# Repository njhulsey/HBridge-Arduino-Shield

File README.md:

# HBridge-Arduino-Shield
During my senior year of highschool I entered the Science Olympiad Electric Vehicle competition. I wanted to make everything for this competition from scratch. My plan was to use as little "pre-made" parts as possible. To control the motors on my car, I made my own arduino H bridge shield. This allowed me to control the direction of each DC motor independently. The H-Bridge IC is the L239D. However, I did not end up using this board in the final competition, but I still learned a lot from making it. I designed the board in eagle and printed it in my highschools makerspace. 

You can read about the competition here: https://scioly.org/wiki/index.php/Electric_Vehicle 

WHAT I LEARNED:
- EAGLE circuit design
- How to use the L239D H Bridge IC
- Soldering
- Circuit board printing
- Learned more about the intricacies of DC motors

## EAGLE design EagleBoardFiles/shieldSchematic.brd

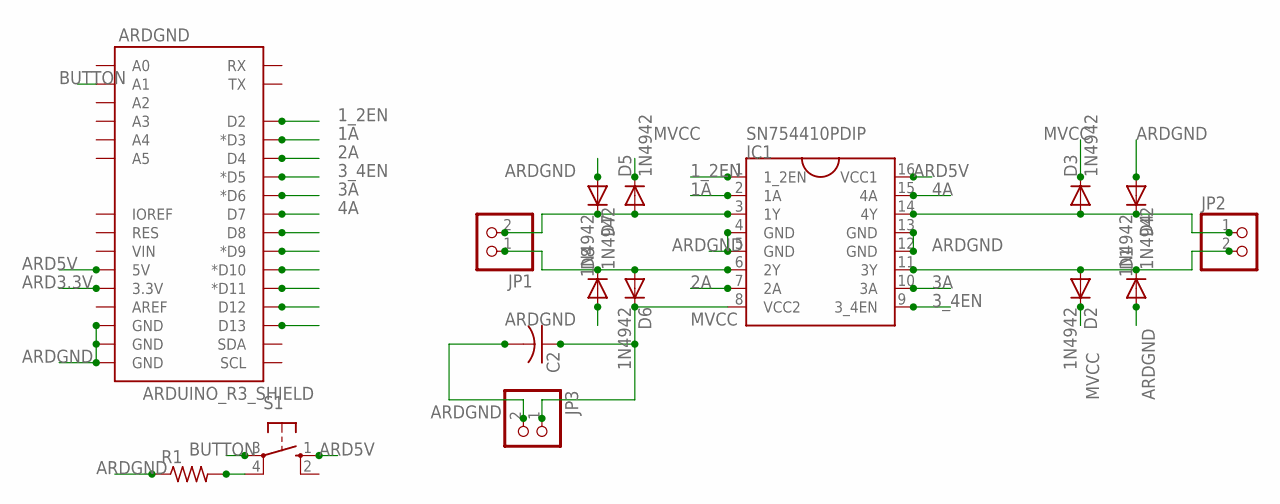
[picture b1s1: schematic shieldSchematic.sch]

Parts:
ARDGND: ARDUINO_R3_SHIELD; UNO_R3_SHIELD
C2: C-US025-024X044; C025-024X044
D1, D2, D3, D4, D5, D6, D7, D8: 1N4942; DO41-10
IC1: SN754410PDIP; DIL16
JP1, JP2, JP3: PINHD-1X2; 1X02
R1: R-US_0207/10; 0207/10
S1: 40-XX; B3F-40XX

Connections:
1A: ARDGND.D3 (*D3), IC1.2 (1A)
1_2EN: ARDGND.D2, IC1.1 (1_2EN)
2A: ARDGND.D4, IC1.7 (2A)
3A: ARDGND.D6 (*D6), IC1.10 (3A)
3_4EN: ARDGND.D5 (*D5), IC1.9 (3_4EN)
4A: ARDGND.D7, IC1.15 (4A)
ARD3.3V: ARDGND.3.3V
ARD5V: ARDGND.5V, IC1.16 (VCC1), S1.1 (S)
ARDGND: ARDGND.GND@0 (GND), ARDGND.GND@1 (GND), ARDGND.GND@2 (GND), C2.2, D1.A, D4.A, D7.A, D8.A, IC1.4 (GND), IC1.5 (GND), IC1.12 (GND), IC1.13 (GND), JP3.2, R1.1
BUTTON: ARDGND.A1, S1.3
MVCC: C2.1, D2.C, D3.C, D5.C, D6.C, IC1.8 (VCC2), JP3.1
unnamed: D5.A, D7.C, IC1.3 (1Y), JP1.2
unnamed: R1.2, S1.4 (P1)
unnamed: D6.A, D8.C, IC1.6 (2Y), JP1.1
unnamed: D1.C, D2.A, IC1.11 (3Y), JP2.2
unnamed: D3.A, D4.C, IC1.14 (4Y), JP2.1

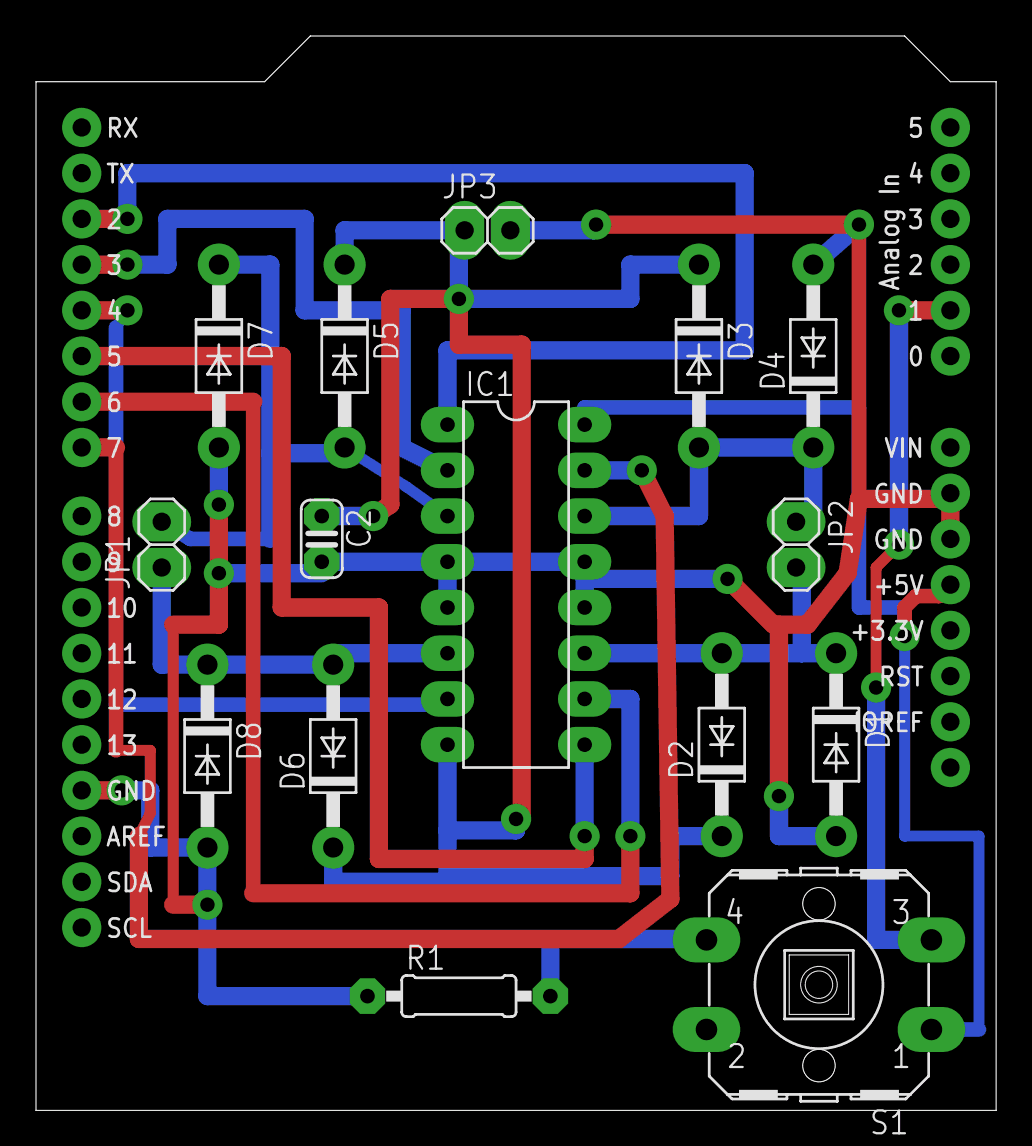
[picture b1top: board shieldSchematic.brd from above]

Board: 2 copper layers, 53.3 x 59.7 mm, 16 parts (0 on the bottom side), 15 nets.

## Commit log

2018-03-11 Create init

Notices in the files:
parts and their libraries:
SparkFun-Boards: Licensing: Creative Commons ShareAlike 4.0 International - https://creativecommons.org/licenses/by-sa/4.0
